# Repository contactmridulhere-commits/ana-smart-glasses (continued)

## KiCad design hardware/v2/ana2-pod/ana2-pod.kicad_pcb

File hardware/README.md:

# ANA V1 temple PCBs

Two KiCad 9 boards that replace the hand-wired V1 modules. Each board is cut in the shape of a glasses
temple (straight, then bending 30° down behind the ear) so it slides into a temple cover. Every part is
soldered directly to the board: the ESP32 chip itself, the sensor chips, the charger and the USB-C socket.

| | Right temple: `ana-main` | Left temple: `ana-power` |
|---|---|---|
| Job | ESP32 + sensors + display link | Battery, charging, power switching |
| Main parts | ESP32-U4WDH (5×5 mm, 4 MB flash in package), 2.4 GHz chip antenna, MAX30102, SHT40, TTP223 touch, 3.3 V and 1.8 V LDOs, side LED, bring-up pads | USB-C (bottom edge), CP2102N USB-serial + DTR/RTS auto-reset, TP4056 charger, DW01A + FS8205A cell protection, USB/battery power path, POWER and BT slide switches, BT-headset power pads, side LED, battery pads |
| Parts | 63: 55 assembled by JLCPCB, 3 tuning parts not fitted, 5 wire/touch/test pads | 48: 44 assembled by JLCPCB, 4 wire/battery pads |

## 3D model of the finished glasses

`3d/index.html` is an interactive model of the whole pair: wayfarer front, hinges, lenses, the OLED pod with its
45° beam splitter, both temple covers, the two real boards with every part fitted, the LiPo, the frame-link and OLED
wiring, the flashlight LEDs and a placeholder for your Bluetooth headset module. Hover any part for its value and
job, switch the covers between solid, see-through and off, explode it, or look through the right lens at the HUD.
It also lists every feature and the weight breakdown (about 43 g as worn, 37–48 g depending on frame and lens
material, without the Bluetooth module).

```bash
python3 -m http.server -d hardware/3d 8000
```

Then open http://localhost:8000 (browsers will not load the models from a `file://` page). After changing a
board, rebuild the board models and part data with `/usr/bin/python3 hardware/3d/make_assembly.py`.

## Shape and size

The outline comes from [`config/temple.json`](config/temple.json): the inside of the temple cover minus
0.3 mm per side (0.5 mm at the ends). Both temples use the same outline: on the right temple the
components face the head; on the left temple they face outwards.

| Cover inside (your input) | Value | PCB |
|---|---|---|
| A straight length, hinge → bend | 105 mm | 104.5 mm |
| B ear-tip length | 40 mm | 39.5 mm |
| θ bend angle | 30° | 30° |
| H1 / H2 / H3 height at hinge / bend / tip | 10 / 8 / 7 mm | 9.4 / 7.4 / 6.4 mm |
| T thickness | 5 mm | 0.8 mm board + max 1.55 mm part (right), 3.3 mm USB-C (left) |

These are the "typical slim temple" numbers you picked. **Measure your real cover and change
`config/temple.json`**, then rebuild (below). [`docs/temple-outline-dimensions.svg`](docs/temple-outline-dimensions.svg)
is a dimensioned drawing with the positions of every window and slot your cover needs; print it 1:1 to check the fit.

Cover openings needed (x measured from the hinge end along the top edge):

- Right temple, head side: MAX30102 window at x ≈ 50–56 mm (must touch skin); SHT40 vent at x ≈ 41–44 mm top edge.
  Touch area on the outer face at x ≈ 26.5–36.5 mm (10 × 4 mm electrode; touch through ≤ 2 mm of plastic).
  Side LED and the two wire bundles leave at the hinge end.
- Left temple: USB-C opening in the bottom edge at x ≈ 16–25 mm; POWER switch lever (top edge, x ≈ 54 mm);
  BT switch lever (top edge, x ≈ 79.5 mm); charge LEDs red/green at x ≈ 40–43 mm.
- The LiPo (≈ 3.5 × 7 × 30 mm, ~60 mAh) sits in the left ear tip; no parts are placed there.

## Layer stack

Both boards are 4-layer, 0.8 mm FR-4 with all parts on the top layer.

| Layer | `ana-main` (right) | `ana-power` (left) |
|---|---|---|
| F.Cu (top) | parts, short links and cross-board hops, RF feed, GND pour | parts, signals, GND pour |
| In1.Cu | solid GND plane (RF reference) | solid GND plane |
| In2.Cu | long signals running along the temple, 3.3 V pour in the free space | signals + GND pour |
| B.Cu (bottom) | long signals running along the temple, touch electrode, GND pour | signals + GND pour |

The ESP32 pins escape through a fixed pattern of short stubs and vias in up to three staggered rows, so
none of its 0.35 mm-pitch pins is boxed in. Its footprint has no bottom-side copper pad (the 16 thermal vias
still tie the exposed pad to the In1 ground plane), so tracks can also pass under the chip. The CP2102N on
the left temple uses the same kind of footprint (9 thermal vias). On the right
temple the long lines run lengthwise on In2 and B.Cu and cross the board on F.Cu, so no track walls off
another; 3.3 V is routed as a net (0.3 mm where it fits) and backed by the 3.3 V pour on In2. Nothing runs
under the touch electrode except its own pad.

## Wiring between the boards

Two thin wire bundles run over the front frame, as in V1:

**Frame link, 8 wires, same pad order on both temples** (pads J1 on the right, J3 on the left):

| Pad | 1 | 2 | 3 | 4 | 5 | 6 | 7 | 8 |
|---|---|---|---|---|---|---|---|---|
| Signal | VSYS | LED_K | GND | EN | IO0 | CHRG | ESP32 RX | ESP32 TX |

All wire pads are plated holes (0.6 mm drill, 1.5 mm pitch): push the stripped wire through and solder. Use flexible
wire (e.g. 32–34 AWG silicone); VSYS and GND carry the whole right temple's current, so use your thickest wire for those
two. USB itself stays on the left temple: the CP2102N there turns it into the ESP32's serial port (RX, TX) and drives
EN/IO0 for automatic flashing, so those four lines are what crosses the frame.

**OLED module, 7 wires** (pads J4 on the right temple, same order as the module's header):
GND, VCC (3.3 V), D0/CLK, D1/MOSI, RES, DC, CS.

Other pads: `EXT_LED` (+/−, optional brighter LED at the frame corner, 68 Ω already on board),
`BT_HEADSET` (+/− switched battery for your Bluetooth headset module), battery `+`/`−`, and on the right
temple four bring-up pads `3V3 GND TX RX` on the ear tip just behind the bend (TX is the ESP32's TX after its
470 Ω series resistor). EN and IO0 are on frame-link pads 4 and 5, so the right temple can also be flashed on its
own from the frame-link pads: 3.6–5 V on VSYS, a 3.3 V USB-serial adapter on RX/TX, and IO0 held to GND while EN is
pulsed low to enter the bootloader.

## What changed from the V1 wiring, and why

| Change | Reason |
|---|---|
| ESP32-U4WDH bare chip instead of the WROOM module | The WROOM is 18 mm wide, taller than the temple. U4WDH is the same dual-core 240 MHz ESP32 with Bluetooth Classic (needed by `SerialBT`) and 4 MB flash inside. Its crystal, RF match and antenna are on the board, following Espressif's reference design. |
| New pin map: OLED CLK/MOSI/CS/DC/RST = 4/23/15/26/27, I²C unchanged (21/22) | U4WDH uses GPIO16/17 for its in-package flash, and on a 7.7 mm-tall board each chip edge can only escape a few signals, so pins were picked by which edge of the chip faces where they go. The firmware has `#define ANA_TEMPLE_PCB 1` with the new pins. |
| SHT40 instead of DHT11 | DHT11 is 12 × 15.5 × 5.5 mm and does not fit a 5 mm temple; SHT40 is 1.5 mm, ±0.2 °C, on the same I²C bus. It sits at the top edge, about 20 mm from the regulator and 45 mm from the ESP32, with no copper pour around it. |
| USB-C flashing (CP2102N + DTR/RTS auto-reset, on the left temple) | Plug in and upload like a devkit; no external programmer. The CP2102N sits next to the USB-C socket, so USB never crosses the frame: only RX, TX, EN and IO0 do. It has its own regulator fed from VSYS, so it is on only while the glasses are on and never back-powers the ESP32. |
| TP4056 + DW01A/FS8205A + power path | Like a protected TP4056 module, but the glasses run from USB while charging so the charger terminates correctly. |
| POWER and BT slide switches (switching MOSFET gates) | The tiny switches only carry gate current; the FETs carry the load. The BT headset is fed from the protected cell directly, never from 5 V. |
| Battery %, USB and charging status to the ESP32 | Shown in the top corner of the HUD. USB is detected from the battery-voltage divider: with USB plugged in, VSYS sits at about 4.6 V (5 V minus a Schottky diode), above any LiPo voltage. The charge-status line has a diode so nothing back-powers the ESP32 when it is off. |
| Touch also read by the ESP32 (GPIO14) | TTP223 is still in toggle mode and switches both temples' LEDs through one MOSFET, like V1; the firmware shows `*` while the light is on. |
| CAP2 RC (3.3 nF ∥ 20 kΩ) left out, only the 10 nF on CAP1 fitted | Espressif marks the RC as optional when deep sleep is not used (it only shortens the deep-sleep transition). Frees space beside the chip. Add it back if you add deep sleep. |
| MAX30102 on the inner face, 1.8 V core LDO on board | Hands-free reading at the temple; I²C is 6 V tolerant so it runs straight from the 3.3 V pull-ups. |

## Checks run on this design

| Check | `ana-main` | `ana-power` |
|---|---|---|
| ERC (`kicad-cli sch erc`) | 0 | 0 |
| Schematic netlist vs `circuits.py` (every pin of every net) | identical | identical |
| DRC (`kicad-cli pcb drc`) errors | 0 | 0 |
| DRC warnings | 1: a 0.08 mm-wide neck in the top-layer ground pour at crystal pad 4 (ground only) | 0 |
| Unconnected items | 0 | 0 |
| Schematic ↔ PCB parity | 0 | 0 |

The reports are in `ana-main/drc.json`, `ana-main/erc.json`, etc. The design rules are JLCPCB's
4-layer limits with margin: 0.1 mm track and space, 0.4/0.2 mm vias, 0.25 mm copper-to-edge.

Not verifiable here, so please check them yourself:

- **RF tuning.** The antenna network (C15/L2/C16 near the chip, C17/R8/C18 near the antenna) uses
  Espressif's starting values. For best range, tune it with a VNA, or at least compare RSSI with your
  phone at a few distances. Keep wires and metal at least 5 mm from the antenna in the ear tip.
- **Fit.** The outline is from typical dimensions until you measure your cover.
- **Firmware.** It was edited carefully but not compiled here (no ESP32 toolchain in this environment).
  Compile it in the Arduino IDE first.

## Ordering at JLCPCB

`fab/<board>/` holds everything needed:

- `<board>-gerbers-jlcpcb.zip`: upload as the PCB. Choose 4 layers, **0.8 mm thickness**, and the standard
  JLC04081H stack-up (impedance control is not required). Any colour.
- `<board>-BOM-jlcpcb.csv` and `<board>-CPL-jlcpcb.csv`: upload for PCBA, top side only. Every part number
  was checked as in stock on 2026-11-07. In the PCBA preview, check the rotation of the ESP32 (pin-1 dot),
  CP2102N, MAX30102, TP4056, the side LEDs (light must point out of the hinge edge) and the USB-C.
- `<board>-BOM-full.csv`: every part, including what you solder yourself (wire pads, battery) and the
  not-fitted RF/touch tuning parts.

## First power-up

1. Inspect the boards and connect the 8-wire frame link, then the OLED. Leave the battery off.
2. Plug USB-C into the left temple with POWER off: the red LED lights (charging), or with no battery the green
   one (the red may flicker), and nothing on the right temple is powered.
3. POWER on: check 3.3 V on the right temple's bring-up pads (`3V3` to `GND`) and 1.8 V across C29 next to the
   MAX30102. The ESP32 shows up as a CP2102N serial port; upload `prototype_toy_.ino` with the Arduino IDE.
4. Solder the battery (red to `+`), then unplug USB and check the HUD shows a battery %.
5. Optional, recommended: burn the flash-voltage eFuse once with `espefuse.py set_flash_voltage 3.3V`, so
   GPIO12 can never select the wrong flash voltage.

## Regenerating

Everything here is generated from Python, so edit the sources, not the KiCad files:

```bash
/usr/bin/python3 hardware/scripts/build.py
```

```bash
/usr/bin/python3 hardware/scripts/export.py
```

- `scripts/circuits.py`: parts, values, LCSC numbers, nets (the single source of truth)
- `config/temple.json`: temple dimensions; `scripts/layouts.py`: part placement
- `scripts/build.py`: schematic → board → routing (`scripts/router.py`, a grid router written for this
  project) → copper pours → ERC/DRC/parity reports
- `scripts/export.py`: Gerbers, drill, BOM/CPL, PDFs, 3D renders, outline drawing

The boards also open normally in KiCad 9 if you want to adjust things by hand (custom symbols and
footprints are in `lib/`).

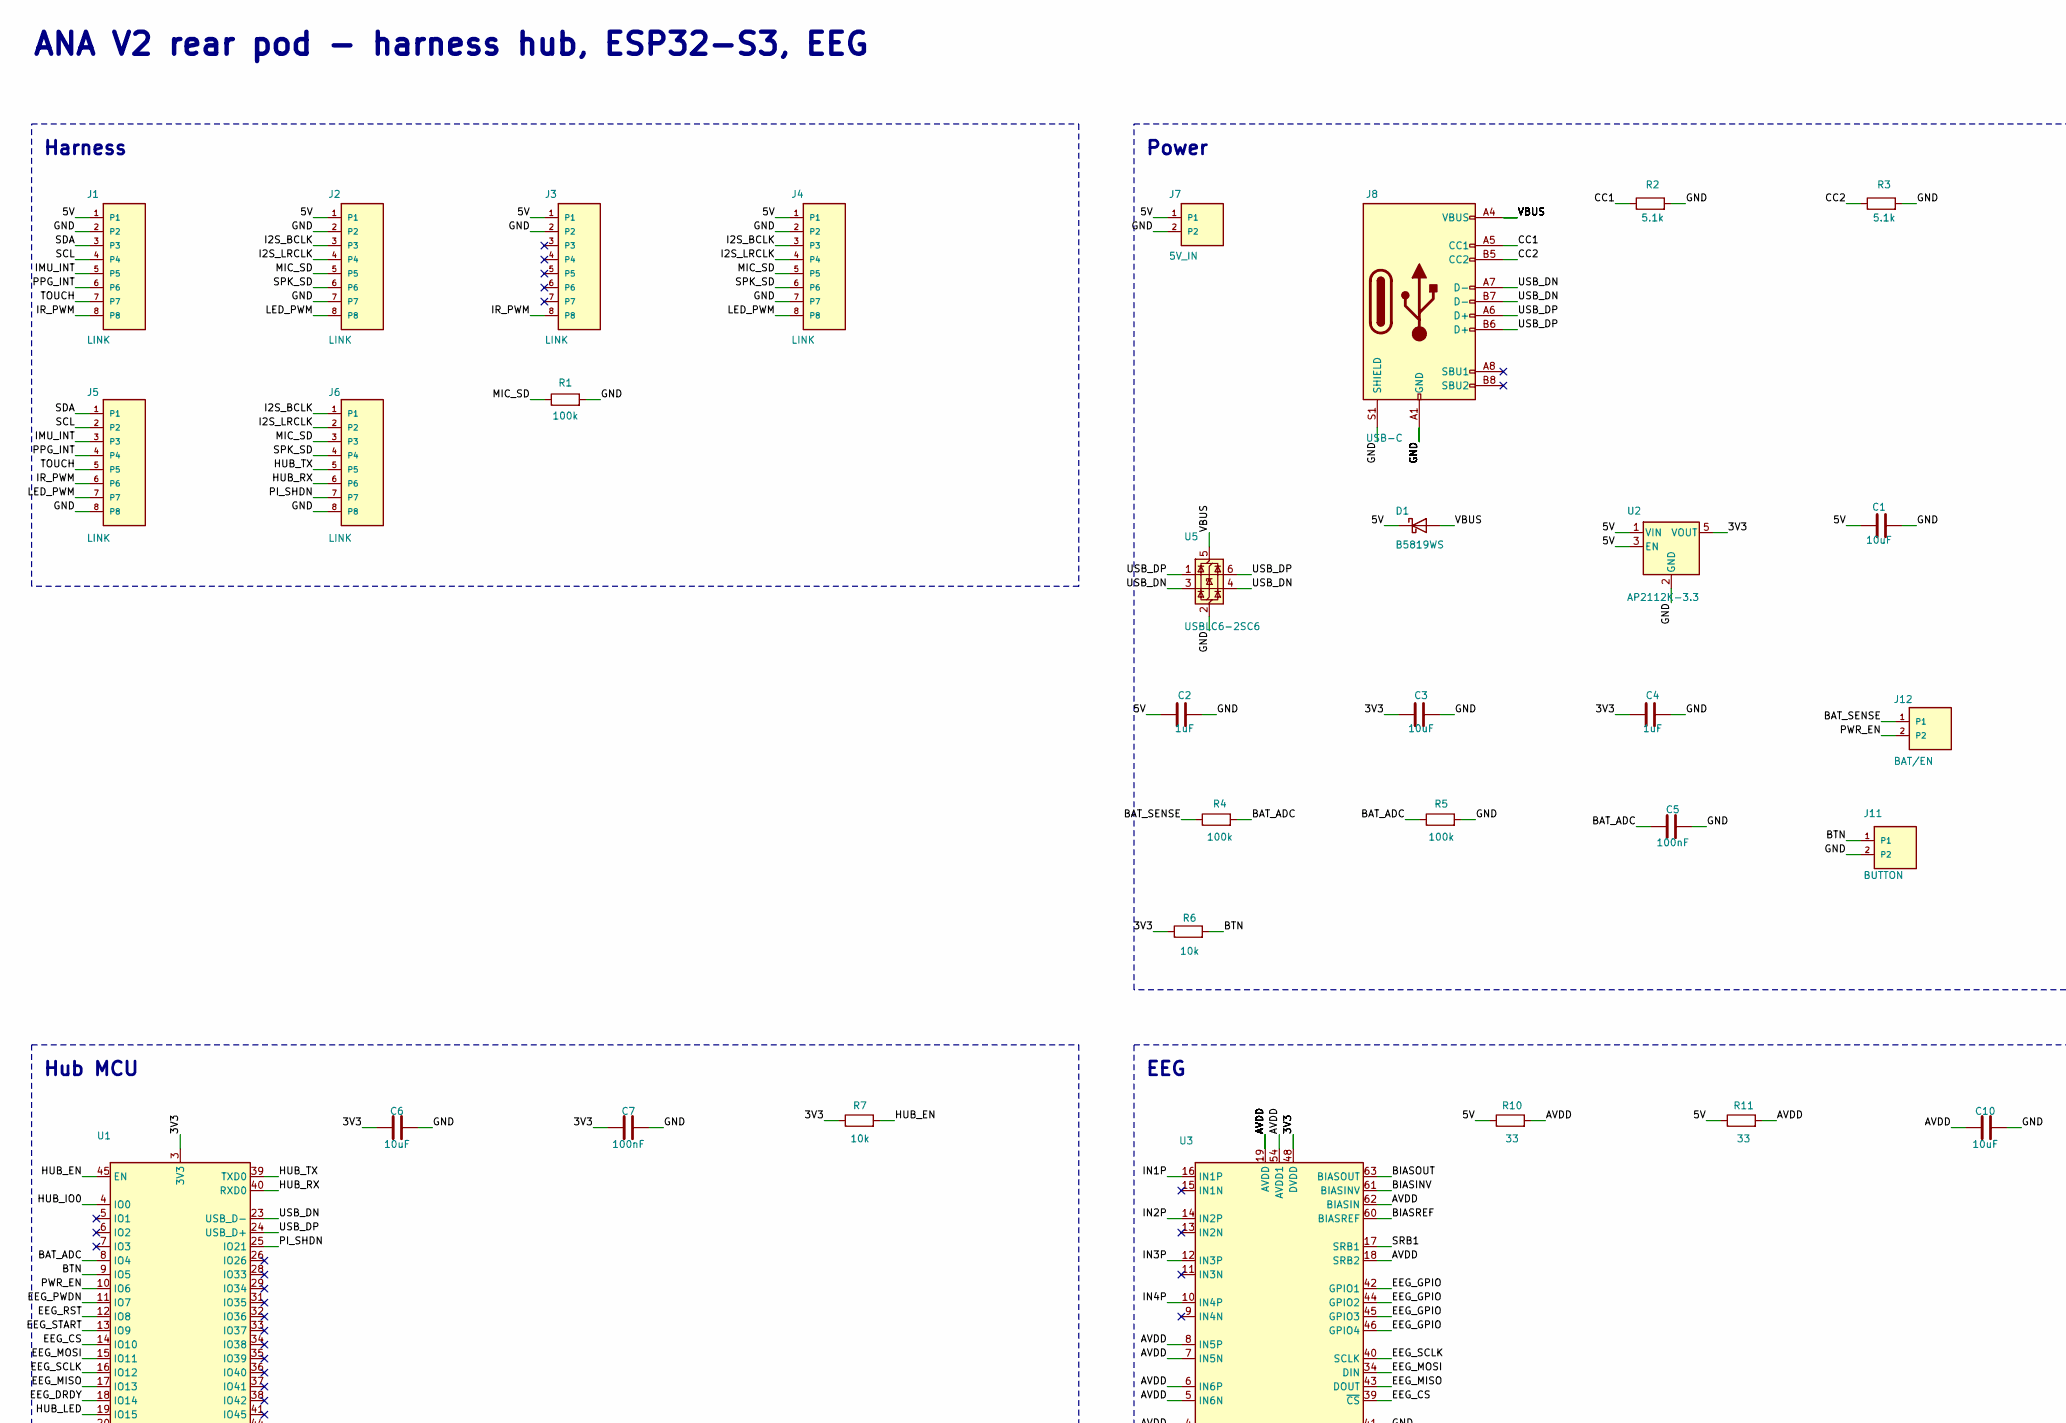
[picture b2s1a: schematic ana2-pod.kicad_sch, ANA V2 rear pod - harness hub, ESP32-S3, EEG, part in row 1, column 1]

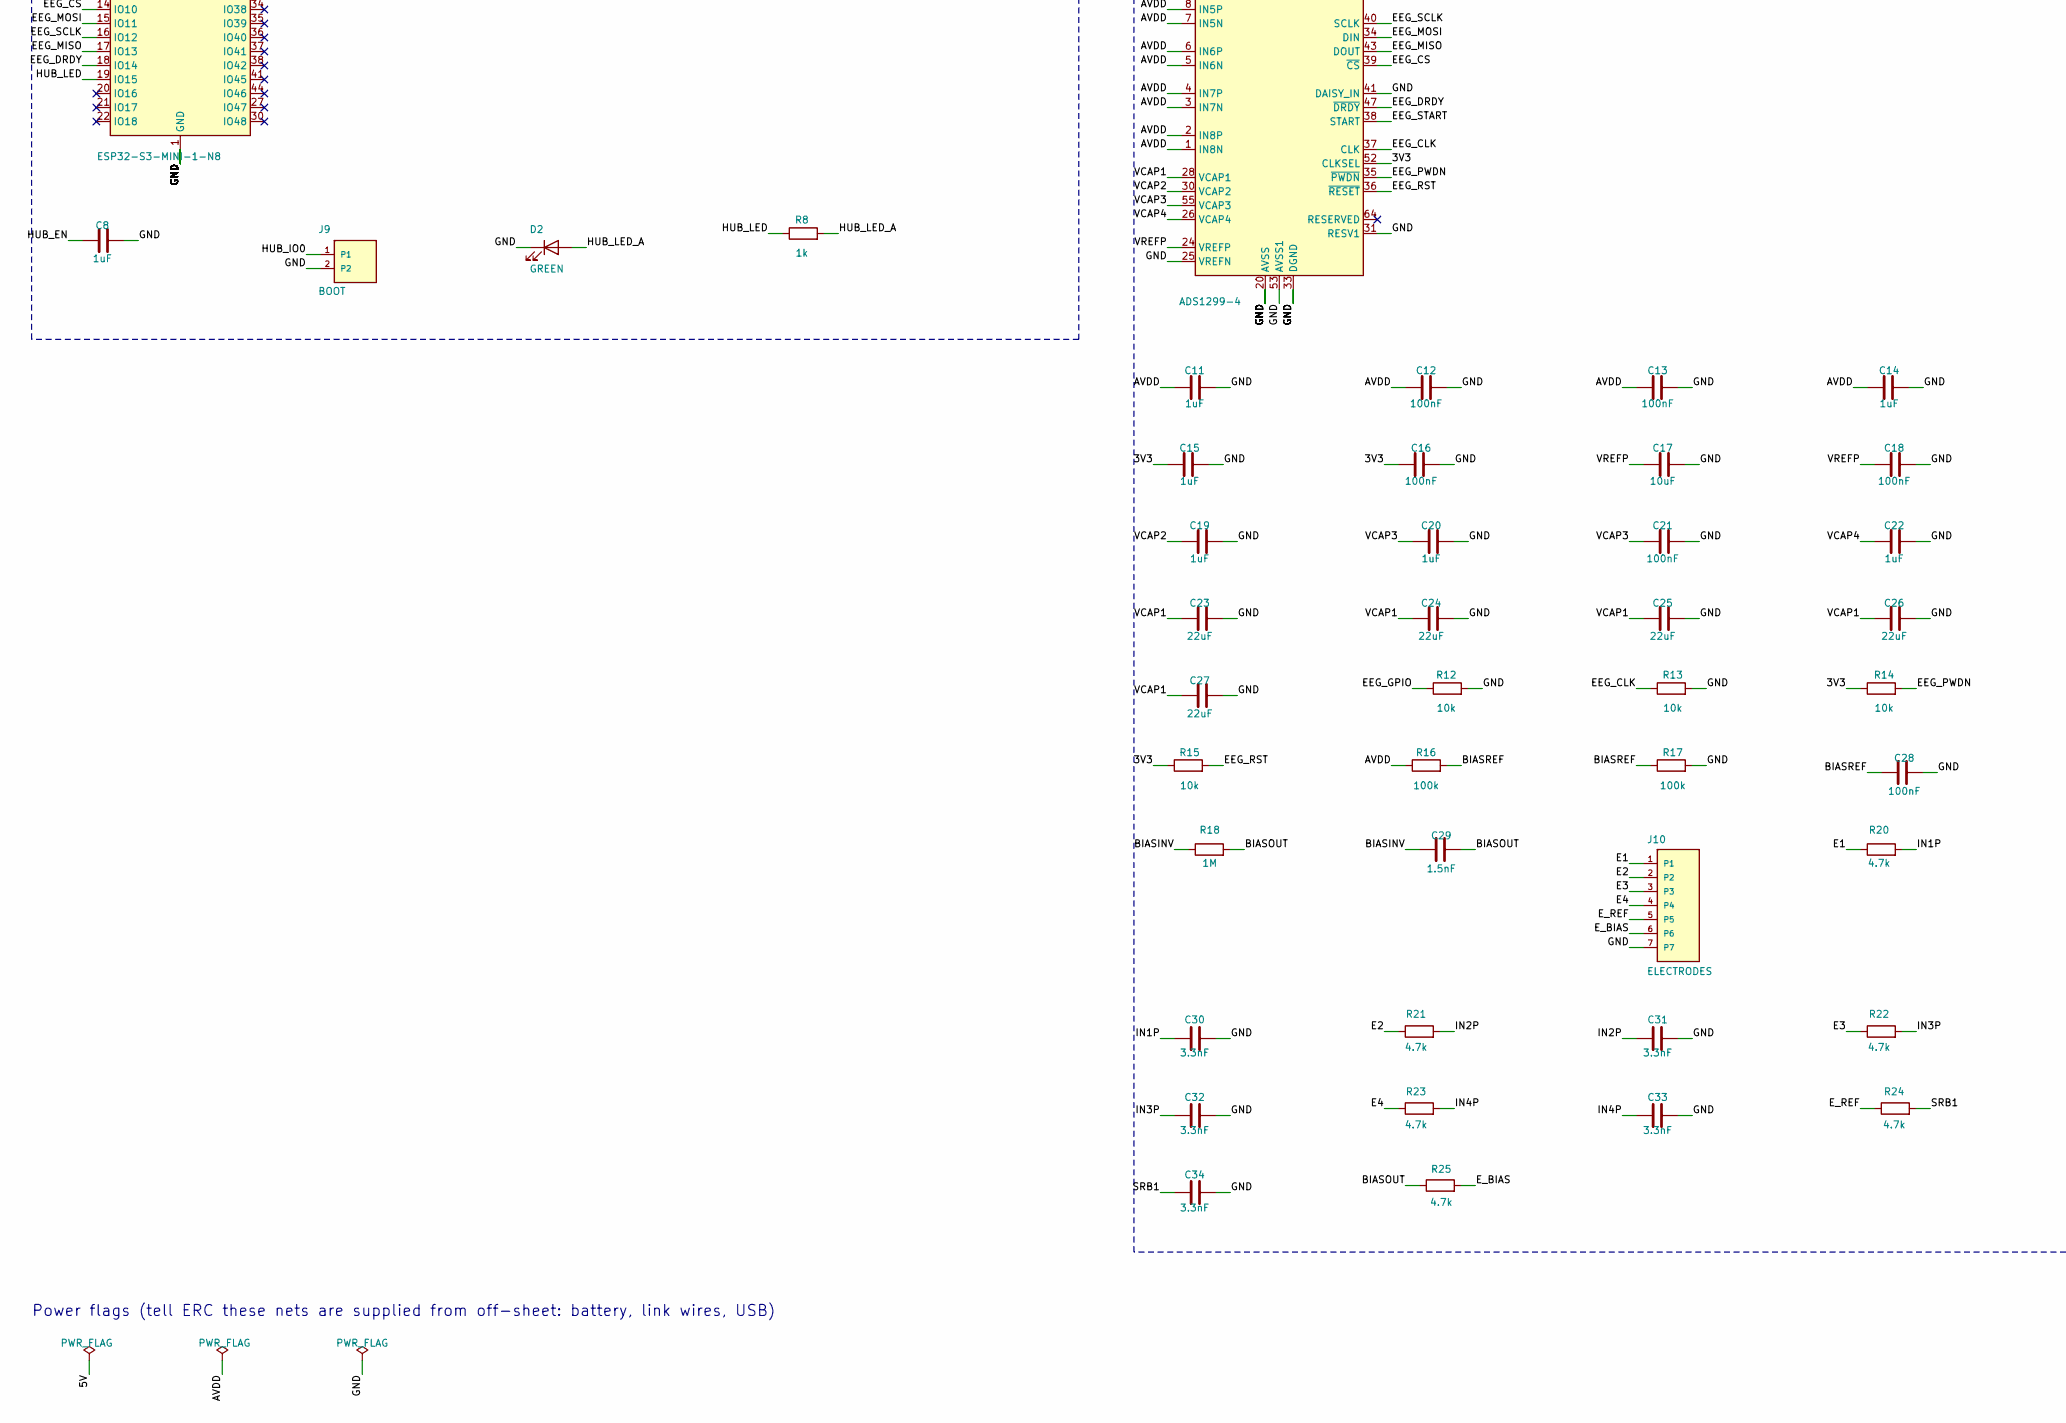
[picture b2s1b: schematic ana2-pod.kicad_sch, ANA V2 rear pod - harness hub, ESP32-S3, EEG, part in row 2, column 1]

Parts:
C1, C10: 10uF; C_0603_1608Metric; LCSC C380317
C2, C4, C8, C11, C14, C15, C19, C20, C22: 1uF; C_0402_1005Metric; LCSC C52923
C3, C6, C17: 10uF; C_0402_1005Metric; LCSC C15525
C5, C7, C12, C13, C16, C18, C21, C28: 100nF; C_0402_1005Metric; LCSC C1525
C23, C24, C25, C26, C27: 22uF; C_0603_1608Metric; LCSC C109448
C29: 1.5nF; C_0402_1005Metric; LCSC C107022
C30, C31, C32, C33, C34: 3.3nF; C_0402_1005Metric; LCSC C107028
D1: B5819WS; D_SOD-323; MPN B5819WS; LCSC C64886
D2: GREEN; LED_0402_1005Metric; MPN NCD0402G1; LCSC C130723
J1, J2, J3, J4, J5, J6: LINK; WirePads_1x08_P1.50mm
J7: 5V_IN; WirePads_1x02_P1.50mm
J8: USB-C; USB_C_Receptacle_HRO_TYPE-C-31-M-12; MPN TYPE-C-31-M-12; LCSC C165948
J9: BOOT; WirePads_1x02_P1.50mm
J10: ELECTRODES; WirePads_1x07_P1.50mm
J11: BUTTON; WirePads_1x02_P1.50mm
J12: BAT/EN; WirePads_1x02_P1.50mm
R1, R4, R5, R16, R17: 100k; R_0402_1005Metric; LCSC C25741
R2, R3: 5.1k; R_0402_1005Metric; LCSC C25905
R6, R7, R12, R13, R14, R15: 10k; R_0402_1005Metric; LCSC C25744
R8: 1k; R_0402_1005Metric; LCSC C11702
R10, R11: 33; R_0402_1005Metric; LCSC C25105
R18: 1M; R_0402_1005Metric; LCSC C26083
R20, R21, R22, R23, R24, R25: 4.7k; R_0402_1005Metric; LCSC C25900
U1: ESP32-S3-MINI-1-N8; ESP32-S2-MINI-1; MPN ESP32-S3-MINI-1-N8; LCSC C2913206
U2: AP2112K-3.3; SOT-23-5; MPN AP2112K-3.3TRG1; LCSC C51118
U3: ADS1299-4; TQFP-64_10x10mm_P0.5mm; MPN ADS1299-4PAGR; LCSC C2651574
U5: USBLC6-2SC6; SOT-23-6; MPN USBLC6-2SC6; LCSC C7519

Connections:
/3V3: C3.1, C4.1, C6.1, C7.1, C15.1, C16.1, R6.1, R7.1, R14.1, R15.1, U1.3 (3V3), U2.5 (VOUT), U3.48 (DVDD), U3.50 (DVDD), U3.52 (CLKSEL)
/5V: C1.1, C2.1, D1.1 (K), J1.1, J2.1, J3.1, J4.1, J7.1, R10.1, R11.1, U2.1 (VIN), U2.3 (EN)
/AVDD: C10.1, C11.1, C12.1, C13.1, C14.1, R10.2, R11.2, R16.1, U3.1 (IN8N), U3.2 (IN8P), U3.3 (IN7N), U3.4 (IN7P), U3.5 (IN6N), U3.6 (IN6P), U3.7 (IN5N), U3.8 (IN5P), U3.18 (SRB2), U3.19 (AVDD), U3.21 (AVDD), U3.22 (AVDD), U3.54 (AVDD1), U3.56 (AVDD), U3.59 (AVDD), U3.62 (BIASIN)
/BAT_ADC: C5.1, R4.2, R5.1, U1.8 (IO4)
/BAT_SENSE: J12.1, R4.1
/BIASINV: C29.1, R18.1, U3.61 (BIASINV)
/BIASOUT: C29.2, R18.2, R25.1, U3.63 (BIASOUT)
/BIASREF: C28.1, R16.2, R17.1, U3.60 (BIASREF)
/BTN: J11.1, R6.2, U1.9 (IO5)
/CC1: J8.A5 (CC1), R2.1
/CC2: J8.B5 (CC2), R3.1
/E1: J10.1, R20.1
/E2: J10.2, R21.1
/E3: J10.3, R22.1
/E4: J10.4, R23.1
/EEG_CLK: R13.1, U3.37 (CLK)
/EEG_CS: U1.14 (IO10), U3.39 (~CS)
/EEG_DRDY: U1.18 (IO14), U3.47 (~DRDY)
/EEG_GPIO: R12.1, U3.42 (GPIO1), U3.44 (GPIO2), U3.45 (GPIO3), U3.46 (GPIO4)
/EEG_MISO: U1.17 (IO13), U3.43 (DOUT)
/EEG_MOSI: U1.15 (IO11), U3.34 (DIN)
/EEG_PWDN: R14.2, U1.11 (IO7), U3.35 (~PWDN)
/EEG_RST: R15.2, U1.12 (IO8), U3.36 (~RESET)
/EEG_SCLK: U1.16 (IO12), U3.40 (SCLK)
/EEG_START: U1.13 (IO9), U3.38 (START)
/E_BIAS: J10.6, R25.2
/E_REF: J10.5, R24.1
/GND: C1.2, C2.2, C3.2, C4.2, C5.2, C6.2, C7.2, C8.2, C10.2, C11.2, C12.2, C13.2, C14.2, C15.2, C16.2, C17.2, C18.2, C19.2, C20.2, C21.2, C22.2, C23.2, C24.2, C25.2, C26.2, C27.2, C28.2, C30.2, C31.2, C32.2, C33.2, C34.2, D2.1 (K), J1.2, J2.2, J2.7, J3.2, J4.2, J4.7, J5.8, J6.8, J7.2, J8.A1 (GND), J8.A12 (GND), J8.B1 (GND), J8.B12 (GND), J8.S1 (SHIELD), J9.2, J10.7, J11.2, R1.2, R2.2, R3.2, R5.2, R12.2, R13.2, R17.2, U1.1 (GND), U1.2 (GND), U1.42 (GND), U1.43 (GND), U1.46 (GND), U1.47 (GND), U1.48 (GND), U1.49 (GND), U1.50 (GND), U1.51 (GND), U1.52 (GND), U1.53 (GND), U1.54 (GND), U1.55 (GND), U1.56 (GND), U1.57 (GND), U1.58 (GND), U1.59 (GND), U1.60 (GND), U1.61 (GND), U1.62 (GND), U1.63 (GND), U1.64 (GND), U1.65 (GND), U2.2 (GND), U3.20 (AVSS), U3.23 (AVSS), U3.25 (VREFN), U3.31 (RESV1), U3.32 (AVSS), U3.33 (DGND), U3.41 (DAISY_IN), U3.49 (DGND), U3.51 (DGND), U3.53 (AVSS1), U3.57 (AVSS), U3.58 (AVSS), U5.2 (GND)
/HUB_EN: C8.1, R7.2, U1.45 (EN)
/HUB_IO0: J9.1, U1.4 (IO0)
/HUB_LED: R8.1, U1.19 (IO15)
/HUB_LED_A: D2.2 (A), R8.2
/HUB_RX: J6.6, U1.40 (RXD0)
/HUB_TX: J6.5, U1.39 (TXD0)
/I2S_BCLK: J2.3, J4.3, J6.1
/I2S_LRCLK: J2.4, J4.4, J6.2
/IMU_INT: J1.5, J5.3
/IN1P: C30.1, R20.2, U3.16 (IN1P)
/IN2P: C31.1, R21.2, U3.14 (IN2P)
/IN3P: C32.1, R22.2, U3.12 (IN3P)
/IN4P: C33.1, R23.2, U3.10 (IN4P)
/IR_PWM: J1.8, J3.8, J5.6
/LED_PWM: J2.8, J4.8, J5.7
/MIC_SD: J2.5, J4.5, J6.3, R1.1
/PI_SHDN: J6.7, U1.25 (IO21)
/PPG_INT: J1.6, J5.4
/PWR_EN: J12.2, U1.10 (IO6)
/SCL: J1.4, J5.2
/SDA: J1.3, J5.1
/SPK_SD: J2.6, J4.6, J6.4
/SRB1: C34.1, R24.2, U3.17 (SRB1)
/TOUCH: J1.7, J5.5
/USB_DN: J8.A7 (D-), J8.B7 (D-), U1.23 (USB_D-), U5.3 (I/O2), U5.4 (I/O2)
/USB_DP: J8.A6 (D+), J8.B6 (D+), U1.24 (USB_D+), U5.1 (I/O1), U5.6 (I/O1)
/VBUS: D1.2 (A), J8.A4 (VBUS), J8.A9 (VBUS), J8.B4 (VBUS), J8.B9 (VBUS), U5.5 (VBUS)
/VCAP1: C23.1, C24.1, C25.1, C26.1, C27.1, U3.28 (VCAP1)
/VCAP2: C19.1, U3.30 (VCAP2)
/VCAP3: C20.1, C21.1, U3.55 (VCAP3)
/VCAP4: C22.1, U3.26 (VCAP4)
/VREFP: C17.1, C18.1, U3.24 (VREFP)

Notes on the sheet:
ANA V2 rear pod - harness hub, ESP32-S3, EEG
Board: 4-layer 0.8 mm FR-4, JLCPCB rules (0.1/0.1 mm, vias 0.4/0.2 mm). All SMT parts on F (top) side.
Temple harness (two rows of 8 wires, same order on temple and pod): A = 5V GND SDA SCL IMU_INT PPG_INT TOUCH IR_PWM | B = 5V GND I2S_BCLK I2S_LRCLK MIC_SD SPK_SD GND LED_PWM
Pi GPIO: SDA 2, SCL 3, IMU_INT 4, PPG_INT 5, PI_SHDN 6, IR_PWM 12, LED_PWM 13, HUB_RX 14 (Pi TXD), HUB_TX 15 (Pi RXD), TOUCH 17, I2S BCLK 18, LRCLK 19, MIC_SD 20, SPK_SD 21
Harness
Power
Hub MCU
EEG
Power flags (tell ERC these nets are supplied from off-sheet: battery, link wires, USB)

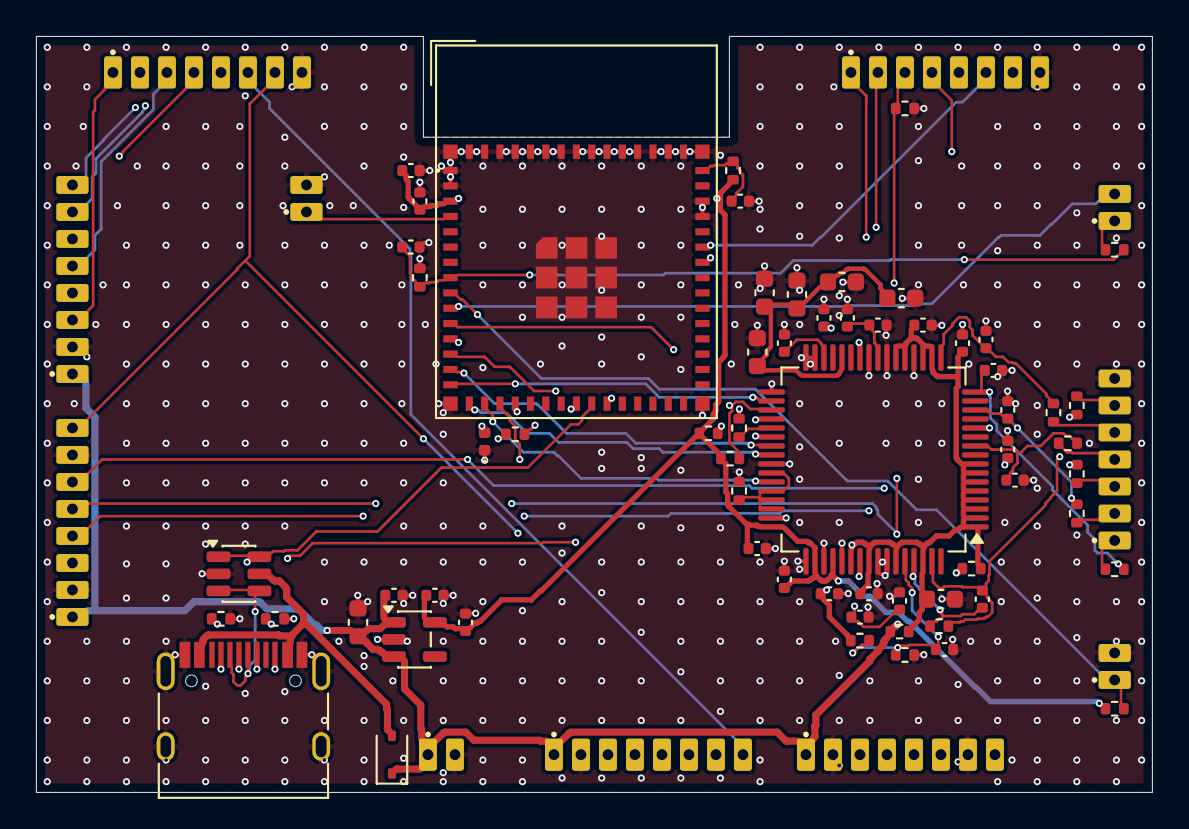
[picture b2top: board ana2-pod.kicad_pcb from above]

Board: 4 copper layers, 62.0 x 42.0 mm, 74 parts (0 on the bottom side), 60 nets.

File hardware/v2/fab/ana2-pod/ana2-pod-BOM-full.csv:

Ref,Value,Footprint,LCSC,MPN,Fitted by,Note
J1,LINK,ana:WirePads_1x08_P1.50mm,,,you (wire/pad),"right temple, row A"
J2,LINK,ana:WirePads_1x08_P1.50mm,,,you (wire/pad),"right temple, row B"
J3,LINK,ana:WirePads_1x08_P1.50mm,,,you (wire/pad),"left temple, row A"
J4,LINK,ana:WirePads_1x08_P1.50mm,,,you (wire/pad),"left temple, row B"
J5,LINK,ana:WirePads_1x08_P1.50mm,,,you (wire/pad),"Raspberry Pi GPIO 2, 3, 4, 5, 17, 12, 13 and GND"
J6,LINK,ana:WirePads_1x08_P1.50mm,,,you (wire/pad),"Raspberry Pi GPIO 18, 19, 20, 21, 15 (RXD), 14 (TXD), 6 and GND"
R1,100k,Resistor_SMD:R_0402_1005Metric,C25741,,JLCPCB,microphone data line pull-down (two mics share it)
J7,5V_IN,ana:WirePads_1x02_P1.50mm,,,you (wire/pad),5 V from the battery pack (+ / -)
J8,USB-C,Connector_USB:USB_C_Receptacle_HRO_TYPE-C-31-M-12,C165948,TYPE-C-31-M-12,JLCPCB,"hub USB: to a Pi USB port, or to a PC for flashing"
R2,5.1k,Resistor_SMD:R_0402_1005Metric,C25905,,JLCPCB,
R3,5.1k,Resistor_SMD:R_0402_1005Metric,C25905,,JLCPCB,
U5,USBLC6-2SC6,Package_TO_SOT_SMD:SOT-23-6,C7519,USBLC6-2SC6,JLCPCB,USB ESD
D1,B5819WS,Diode_SMD:D_SOD-323,C64886,B5819WS,JLCPCB,USB can power the hub when the battery pack is off
U2,AP2112K-3.3,Package_TO_SOT_SMD:SOT-23-5,C51118,AP2112K-3.3TRG1,JLCPCB,
C1,10uF,Capacitor_SMD:C_0603_1608Metric,C380317,,JLCPCB,
C2,1uF,Capacitor_SMD:C_0402_1005Metric,C52923,,JLCPCB,
C3,10uF,Capacitor_SMD:C_0402_1005Metric,C15525,,JLCPCB,
C4,1uF,Capacitor_SMD:C_0402_1005Metric,C52923,,JLCPCB,
J12,BAT/EN,ana:WirePads_1x02_P1.50mm,,,you (wire/pad),1: cell voltage for the gauge  2: enable output for the pack
R4,100k,Resistor_SMD:R_0402_1005Metric,C25741,,JLCPCB,cell voltage / 2
R5,100k,Resistor_SMD:R_0402_1005Metric,C25741,,JLCPCB,
C5,100nF,Capacitor_SMD:C_0402_1005Metric,C1525,,JLCPCB,
J11,BUTTON,ana:WirePads_1x02_P1.50mm,,,you (wire/pad),power / wake button
R6,10k,Resistor_SMD:R_0402_1005Metric,C25744,,JLCPCB,
U1,ESP32-S3-MINI-1-N8,RF_Module:ESP32-S2-MINI-1,C2913206,ESP32-S3-MINI-1-N8,JLCPCB,"always-on hub: power button, battery level, EEG stream, BLE"
C6,10uF,Capacitor_SMD:C_0402_1005Metric,C15525,,JLCPCB,
C7,100nF,Capacitor_SMD:C_0402_1005Metric,C1525,,JLCPCB,
R7,10k,Resistor_SMD:R_0402_1005Metric,C25744,,JLCPCB,
C8,1uF,Capacitor_SMD:C_0402_1005Metric,C52923,,JLCPCB,EN delay
J9,BOOT,ana:WirePads_1x02_P1.50mm,,,you (wire/pad),short while plugging USB to force the bootloader
D2,GREEN,LED_SMD:LED_0402_1005Metric,C130723,NCD0402G1,JLCPCB,status
R8,1k,Resistor_SMD:R_0402_1005Metric,C11702,,JLCPCB,
U3,ADS1299-4,Package_QFP:TQFP-64_10x10mm_P0.5mm,C2651574,ADS1299-4PAGR,JLCPCB,4-channel 24-bit EEG front end; inputs 1-4 against the reference on SRB1
R10,33,Resistor_SMD:R_0402_1005Metric,C25105,,JLCPCB,analog supply filter (2 x 33R with 12 uF)
R11,33,Resistor_SMD:R_0402_1005Metric,C25105,,JLCPCB,
C10,10uF,Capacitor_SMD:C_0603_1608Metric,C380317,,JLCPCB,
C11,1uF,Capacitor_SMD:C_0402_1005Metric,C52923,,JLCPCB,
C12,100nF,Capacitor_SMD:C_0402_1005Metric,C1525,,JLCPCB,
C13,100nF,Capacitor_SMD:C_0402_1005Metric,C1525,,JLCPCB,
C14,1uF,Capacitor_SMD:C_0402_1005Metric,C52923,,JLCPCB,AVDD1
C15,1uF,Capacitor_SMD:C_0402_1005Metric,C52923,,JLCPCB,DVDD
C16,100nF,Capacitor_SMD:C_0402_1005Metric,C1525,,JLCPCB,
C17,10uF,Capacitor_SMD:C_0402_1005Metric,C15525,,JLCPCB,reference
C18,100nF,Capacitor_SMD:C_0402_1005Metric,C1525,,JLCPCB,
C19,1uF,Capacitor_SMD:C_0402_1005Metric,C52923,,JLCPCB,
C20,1uF,Capacitor_SMD:C_0402_1005Metric,C52923,,JLCPCB,
C21,100nF,Capacitor_SMD:C_0402_1005Metric,C1525,,JLCPCB,
C22,1uF,Capacitor_SMD:C_0402_1005Metric,C52923,,JLCPCB,
C23,22uF,Capacitor_SMD:C_0603_1608Metric,C109448,,JLCPCB,"VCAP1, 5 x 22 uF"
C24,22uF,Capacitor_SMD:C_0603_1608Metric,C109448,,JLCPCB,
C25,22uF,Capacitor_SMD:C_0603_1608Metric,C109448,,JLCPCB,
C26,22uF,Capacitor_SMD:C_0603_1608Metric,C109448,,JLCPCB,
C27,22uF,Capacitor_SMD:C_0603_1608Metric,C109448,,JLCPCB,
R12,10k,Resistor_SMD:R_0402_1005Metric,C25744,,JLCPCB,unused GPIO1-4
R13,10k,Resistor_SMD:R_0402_1005Metric,C25744,,JLCPCB,CLK unused
R14,10k,Resistor_SMD:R_0402_1005Metric,C25744,,JLCPCB,
R15,10k,Resistor_SMD:R_0402_1005Metric,C25744,,JLCPCB,
R16,100k,Resistor_SMD:R_0402_1005Metric,C25741,,JLCPCB,mid-supply bias reference
R17,100k,Resistor_SMD:R_0402_1005Metric,C25741,,JLCPCB,
C28,100nF,Capacitor_SMD:C_0402_1005Metric,C1525,,JLCPCB,
R18,1M,Resistor_SMD:R_0402_1005Metric,C26083,,JLCPCB,bias amplifier feedback (datasheet: 1M || 1.5 nF)
C29,1.5nF,Capacitor_SMD:C_0402_1005Metric,C107022,,JLCPCB,
J10,ELECTRODES,ana:WirePads_1x07_P1.50mm,,,you (wire/pad),"dry electrodes: 1 left ear tip, 2 right ear tip, 3 left temple, 4 right temple, 5 reference (nose pad), 6 bias (other nose pad), 7 cable shield"
R20,4.7k,Resistor_SMD:R_0402_1005Metric,C25900,,JLCPCB,input protection + RF filter
C30,3.3nF,Capacitor_SMD:C_0402_1005Metric,C107028,,JLCPCB,
R21,4.7k,Resistor_SMD:R_0402_1005Metric,C25900,,JLCPCB,
C31,3.3nF,Capacitor_SMD:C_0402_1005Metric,C107028,,JLCPCB,
R22,4.7k,Resistor_SMD:R_0402_1005Metric,C25900,,JLCPCB,
C32,3.3nF,Capacitor_SMD:C_0402_1005Metric,C107028,,JLCPCB,
R23,4.7k,Resistor_SMD:R_0402_1005Metric,C25900,,JLCPCB,
C33,3.3nF,Capacitor_SMD:C_0402_1005Metric,C107028,,JLCPCB,
R24,4.7k,Resistor_SMD:R_0402_1005Metric,C25900,,JLCPCB,
C34,3.3nF,Capacitor_SMD:C_0402_1005Metric,C107028,,JLCPCB,
R25,4.7k,Resistor_SMD:R_0402_1005Metric,C25900,,JLCPCB,bias electrode drive
